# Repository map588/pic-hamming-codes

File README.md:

# PIC Parity Bit Error Detection Game

A PIC16F818 microcontroller-based educational game that teaches error detection using Hamming code parity bits through an interactive LED matrix display.

## Project Overview

This project implements a 4x4 LED grid game where players must identify and correct single-bit errors in transmitted data using parity bits. The system displays random data with intentional errors, and players use buttons to select and correct the flipped bit. 

I was inspired to make the project by [this excellant video](https://youtu.be/wTJI_WuZSwE?si=To3kZnW4QarjRsSB) by 3Blue1Brown on youtube.  Its really good, you should go watch it, its way better than my boring assembly code. 

### Key Features
- 4x4 LED matrix displaying random data patterns
- 4 parity bit indicators showing error detection codes
- Interactive button controls for bit selection and confirmation
- Visual feedback for correct/incorrect solutions
- Random number generation for varied gameplay

## Game Mechanics

1. **Display**: A 4x4 grid shows random on/off LEDs representing transmitted data
2. **Parity Bits**: 4 LEDs indicate parity for different bit groupings:
   - Bit 0: Columns 1 and 3 parity
   - Bit 1: Columns 2 and 4 parity  
   - Bit 2: Rows 1 and 3 parity
   - Bit 3: Rows 2 and 4 parity
3. **Objective**: Identify which bit in the 4x4 grid has been flipped
4. **Controls**:
   - Selection button: Cycle through grid positions (current selection blinks)
   - Confirm button: Lock in selection and check answer
   - Reset button: Generate new puzzle

### Feedback System
- **Correct Answer**: Diagonal checkmark animation on grid, all parity bits flash
- **Wrong Answer**: X pattern on grid, parity bits alternate

## Hardware

### Components
- **Microcontroller**: PIC16F818
- **Display**: 4x4 LED matrix + 4 parity indicator LEDs
- **Input**: 3 push buttons (select, confirm, reset)
- **Power**: Standard 5V supply

### Circuit Design
- Custom PCB design created in KiCad
- Surface-mount components for compact design
- ICSP programming header for development

*Custom PCB layout showing component placement and routing*

*Circuit schematic with PIC16F818 microcontroller and LED matrix*

*Final assembled PCB showing the completed hardware*

## Software

### Architecture
- **Language**: PIC Assembly (MPASM)
- **Random Number Generator**: X-ABC algorithm implementation
- **Interrupt Handling**: Button debouncing and timing
- **Display Control**: LED matrix multiplexing
- **Game Logic**: Hamming code parity calculation and verification

### Key Technical Challenges

#### Interrupt-Driven Display Multiplexing
The most complex aspect was implementing precise timer interrupt handling for LED matrix control:

- **8-bit Timer Interrupt**: With only an 8-bit timer, careful cycle counting was required to utilize the interrupt effectively 
- **Manual Context Switching**: PIC16F818 has no automatic stack - all register preservation (W, STATUS, FSR) must be handled manually in the ISR
- **Dual Display Timing**: The interrupt cycles through two 4x4 display boards, using an 8-pin indexing system
- **Memory Architecture**: 4 bytes per board (8 total), with MSB controlling row transistors and 4 LSBs selecting column LEDs
- **Persistence of Vision**: Timer frequency tuned so LEDs appear continuously lit despite sequential scanning
- **Input Responsiveness**: ISR timing balanced to maintain button polling responsiveness - if interrupts run too long, user input is missed

This required hours of timing analysis and empirical tuning to achieve both visual persistence and real-time user interaction.

#### Bit-by-Bit Board Traversal Edge Cases
The scan_routine implements a complex state machine for traversing the 4x4 board one bit at a time, with several critical edge cases:

- **Bit Position Tracking**: BITCOUNTER (0-3) tracks position within each row, while BITCHECK holds the actual bit mask being shifted left via `rlf` to traverse columns
- **Row Boundary Detection**: When BITCOUNTER reaches 4 (checked via `btfsc BITCOUNTER,2`), the end_row routine handles:
  - XORing the last bit of the current row
  - Incrementing FSR to move to the next row
  - Resetting BITCOUNTER to 0 and BITCHECK to 0x18 for the next row
- **Special First Bit Handling**: When BITCOUNTER is 0 (start of row), a different literal is XORed with the COPY board due to the boundary with the column bits 
- **ROWCHECK Wraparound**: ROWCHECK tracks the current row (0x24-0x27 for BOARDCPY), with bit 3 tested to detect when all 4 rows are complete, triggering a reset to the first row
- **Debounce Timing**: Each button press includes a delay (0xC0) to prevent multiple triggers from a single press while maintaining responsiveness

This state machine allows users to select any single bit in the 4x4 grid despite having only one selection button, by cycling through all 16 positions sequentially.

#### Automatic Board Swapping via Timer Interrupt
The system implements an elegant visual effect where two boards (BOARDPTR and BOARDCPY) are "automagically" swapped at human-visible intervals:

- **Timer-Driven Display**: TMR0 overflow triggers the interrupt service routine, which calls `display_both`
- **Asymmetric Display Timing**: 
  - BOARDPTR displays for 16 iterations (4 LEDs × 4 rows × 255 delay cycles)
  - BOARDCPY displays for 64 iterations (4× longer) to emphasize the modified state
  - This creates a visual "blink" effect where changes are clearly visible
- **Memory Layout**: Two consecutive 4-byte blocks in RAM:
  - BOARDPTR (0x20-0x23): Original puzzle state
  - BOARDCPY (0x24-0x27): User-modified state with bit flips
- **Multiplexed Column Driving**: PORTB drives transistor bases with patterns 0x08, 0x04, 0x02, 0x01 to enable each column sequentially
- **Human Persistence of Vision**: Cycling through all positions (faster than ~30Hz) makes both boards appear simultaneously lit with the modified bits appearing to blink

## Project Structure

```
├── hardware/
│   ├── pcb/              # KiCad PCB files
│   ├── schematics/       # Schematic designs
│   ├── gerbers/          # Manufacturing files
│   └── libraries/        # Custom component libraries
├── software/
│   ├── src/              # PIC assembly source code
├── docs/
│   ├── images/           # Project photos and screenshots
│   ├── datasheets/       # Component specifications
│   └── Final_Project_Idea.txt  # Original project concept
└── manufacturing/        # Production files
```

## License

This project is open source and available for educational use. The random number generator algorithm is freely available but not suitable for cryptographic applications.

---

*Developed as a final project demonstrating embedded systems design, PCB layout, and error detection algorithms.*

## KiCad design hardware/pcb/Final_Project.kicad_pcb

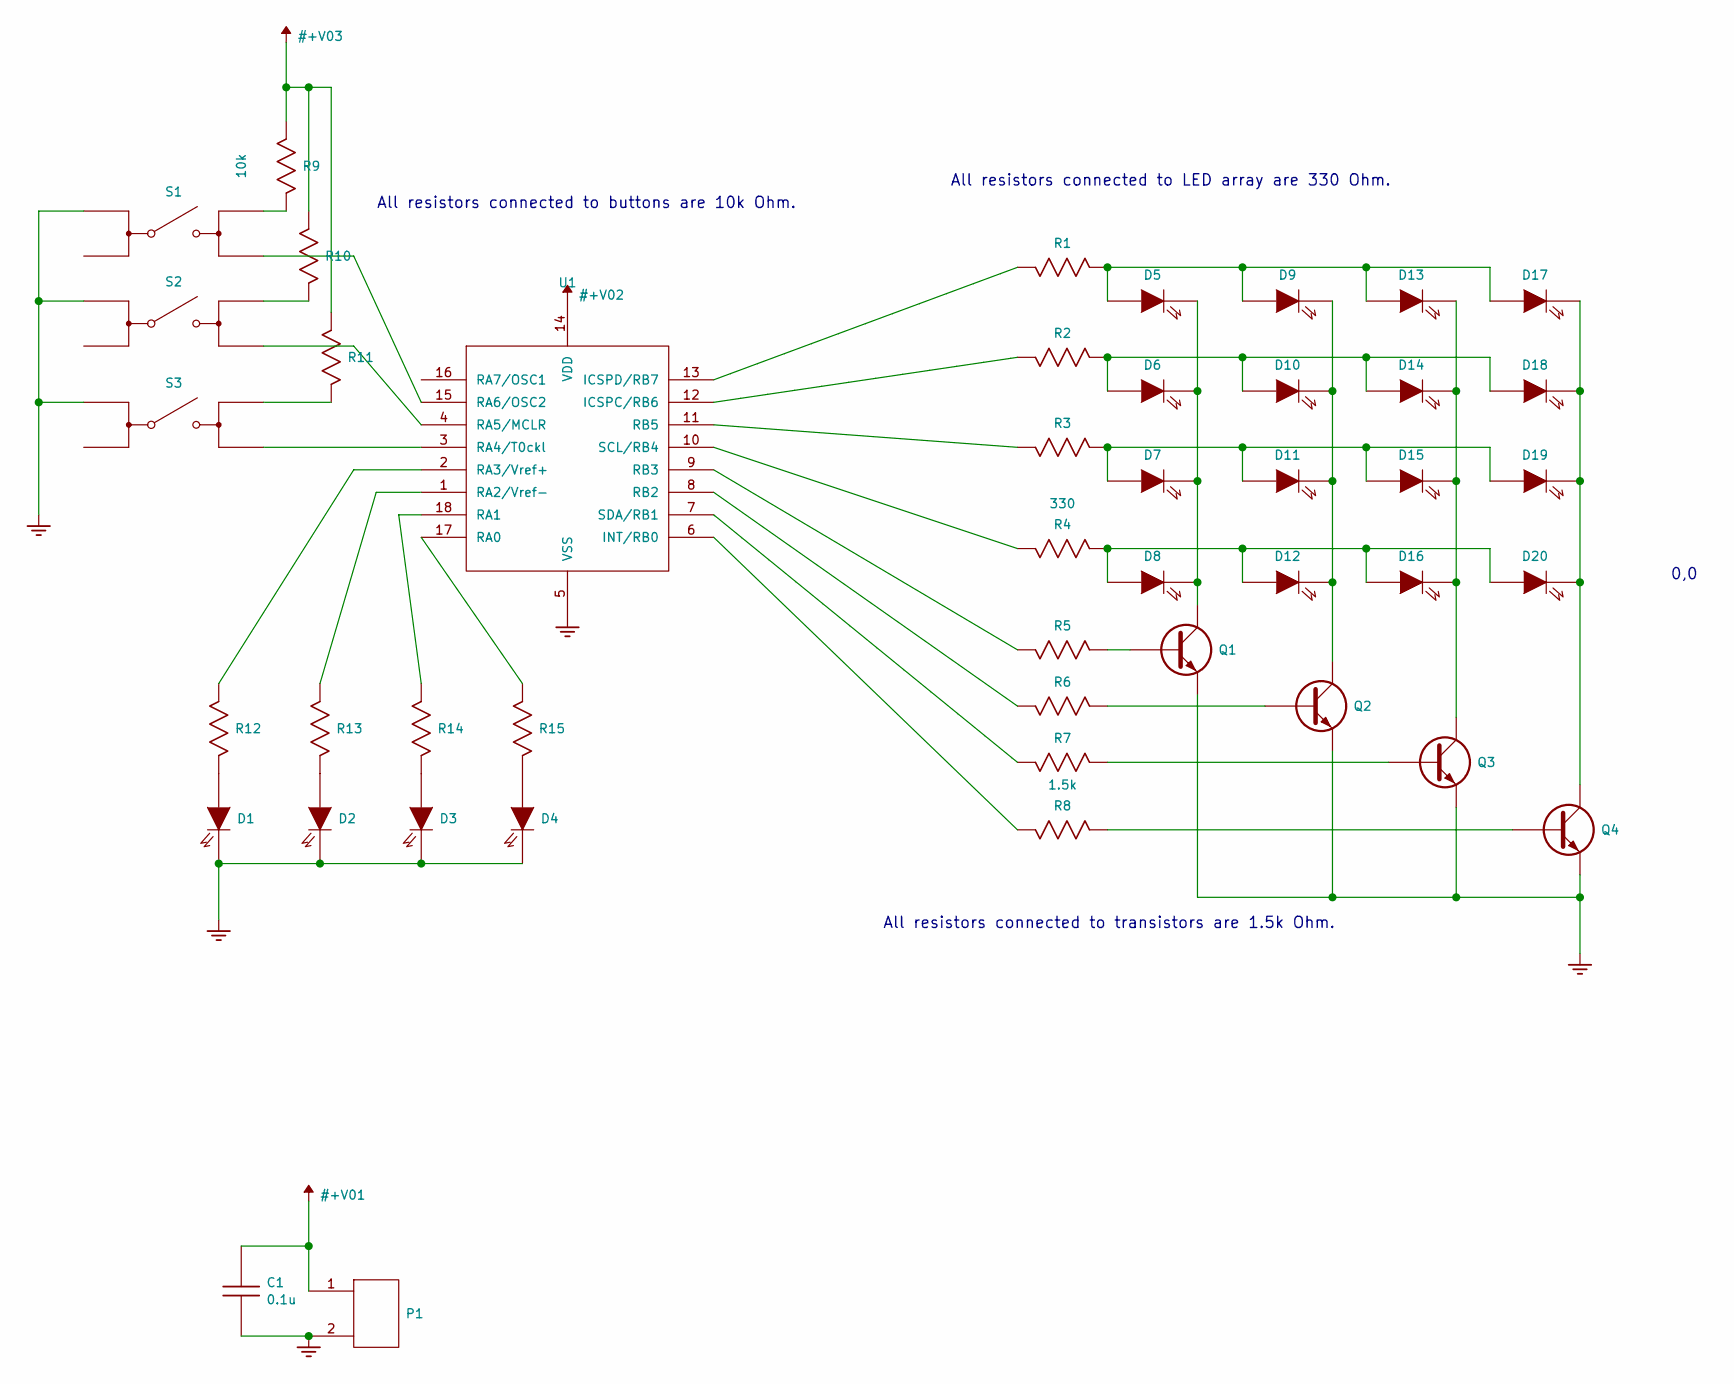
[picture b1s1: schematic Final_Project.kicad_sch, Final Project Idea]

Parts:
C1: 0.1u; SM1206
D1, D2, D3, D4, D5, D6, D7, D8, D9, D10, D11, D12, D13, D14, D15, D16, D17, D18, D19, D20: SVC_LED; SM1206-D_LED
P1: SVC_CONN_2PIN; 2-PIN-Power
Q1, Q2, Q3, Q4: SVC_Q_MMBT3904L; SOT23
R1, R2, R3, R4, R12, R13, R14, R15: 330; SM1206-R_C
R5, R6, R7, R8: 1.5k; SM1206-R_C
R9, R10, R11: 10k; SM1206-R_C
S1, S2, S3: SVC_BUTTON_SWITCH; BUTTON-SWITCH-SPST
U1: SVC_PIC16F818-18PDIP; SM_DIP18-300

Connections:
+V: C1.1, P1.1, R9.1, R10.1, R11.1, U1.14 (VDD)
GND: C1.2, D1.2 (K), D2.2 (K), D3.2 (K), D4.2 (K), P1.2 (PM), Q1.2 (E), Q2.2 (E), Q3.2 (E), Q4.2 (E), S1.3, S2.3, S3.3, U1.5 (VSS)
unnamed: D1.1 (A), R12.2
unnamed: D2.1 (A), R13.2
unnamed: D3.1 (A), R14.2
unnamed: D4.1 (A), R15.2
unnamed: D5.2 (K), D6.2 (K), D7.2 (K), D8.2 (K), Q1.3 (C)
unnamed: D6.1 (A), D10.1 (A), D14.1 (A), D18.1 (A), R2.1
unnamed: D9.2 (K), D10.2 (K), D11.2 (K), D12.2 (K), Q2.3 (C)
unnamed: D7.1 (A), D11.1 (A), D15.1 (A), D19.1 (A), R3.1
unnamed: D8.1 (A), D12.1 (A), D16.1 (A), D20.1 (A), R4.1
unnamed: D5.1 (A), D9.1 (A), D13.1 (A), D17.1 (A), R1.1
unnamed: D13.2 (K), D14.2 (K), D15.2 (K), D16.2 (K), Q3.3 (C)
unnamed: D17.2 (K), D18.2 (K), D19.2 (K), D20.2 (K), Q4.3 (C)
unnamed: Q1.1 (B), R5.1
unnamed: Q2.1 (B), R6.1
unnamed: Q3.1 (B), R7.1
unnamed: Q4.1 (B), R8.1
unnamed: R1.2, U1.13 (ICSPD/RB7)
unnamed: R2.2, U1.12 (ICSPC/RB6)
unnamed: R3.2, U1.11 (RB5)
unnamed: R4.2, U1.10 (SCL/RB4)
unnamed: R5.2, U1.9 (RB3)
unnamed: R6.2, U1.8 (RB2)
unnamed: R7.2, U1.7 (SDA/RB1)
unnamed: R8.2, U1.6 (INT/RB0)
unnamed: R9.2, S1.1
unnamed: R10.2, S2.1
unnamed: R11.2, S3.1
unnamed: R12.1, U1.2 (RA3/Vref+)
unnamed: R13.1, U1.1 (RA2/Vref-)
unnamed: R14.1, U1.18 (RA1)
unnamed: R15.1, U1.17 (RA0)
unnamed: S1.2, U1.15 (RA6/OSC2)
unnamed: S2.2, U1.4 (RA5/MCLR)
unnamed: S3.2, U1.3 (RA4/T0ckl)

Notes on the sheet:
All resistors connected to buttons are 10k Ohm.
All resistors connected to transistors are 1.5k Ohm.
All resistors connected to LED array are 330 Ohm.
0,0

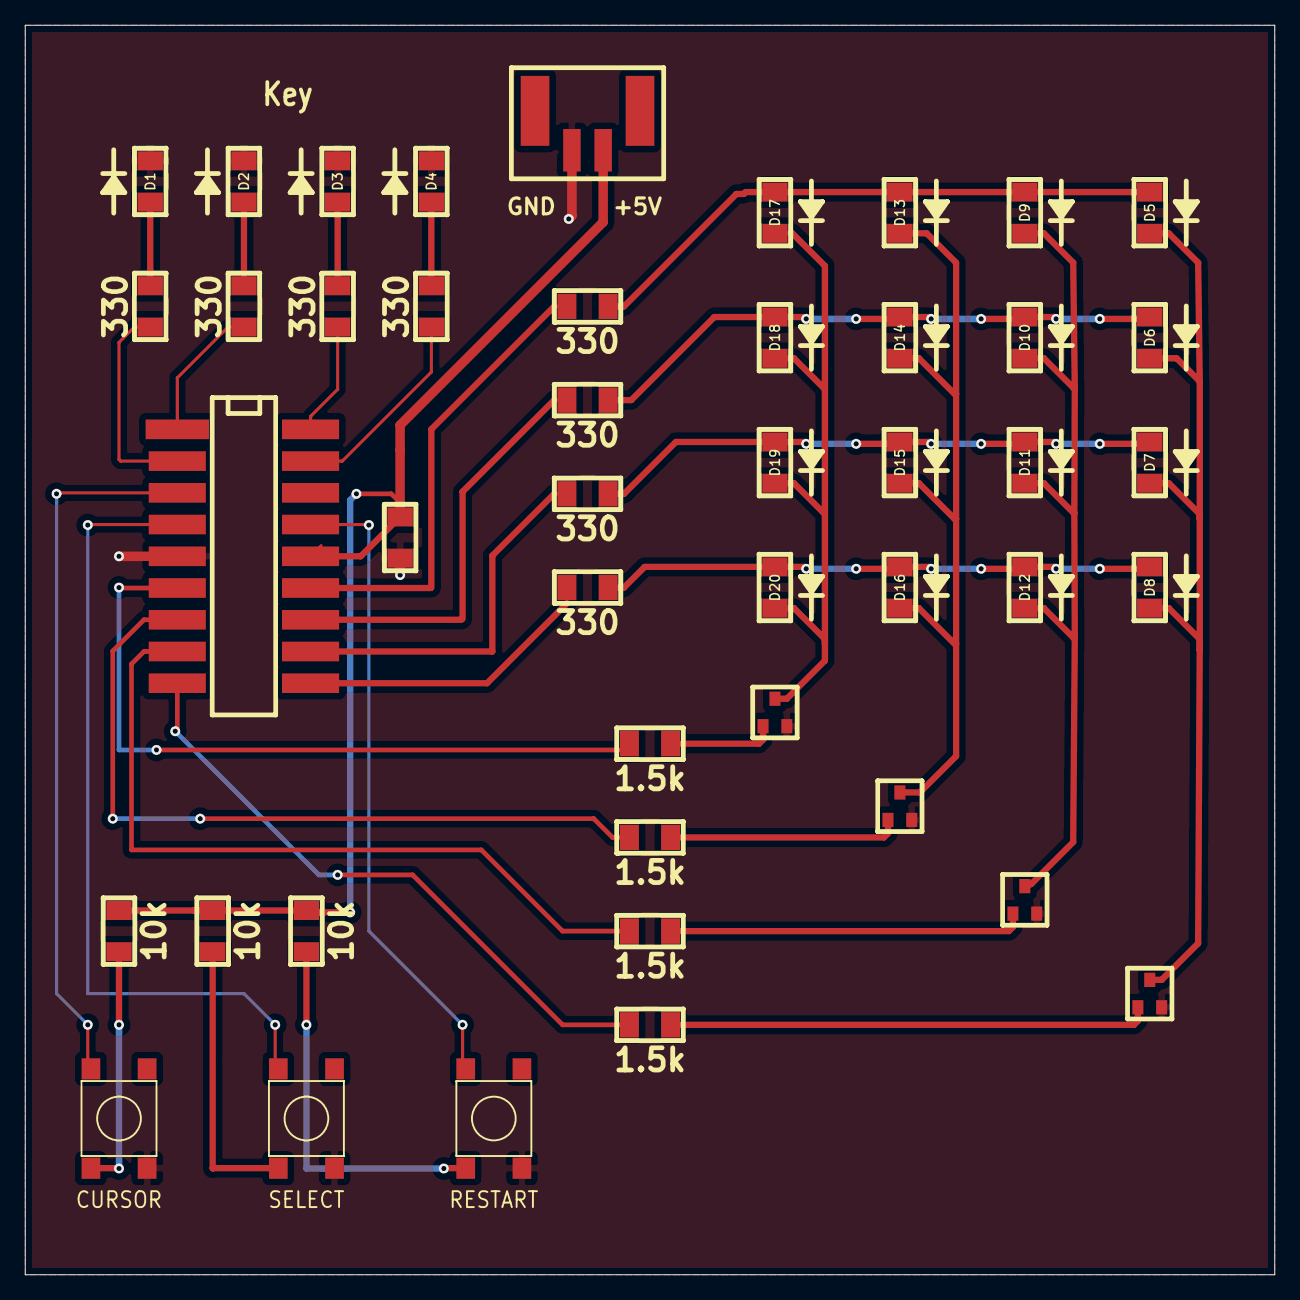
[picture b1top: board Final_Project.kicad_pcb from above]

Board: 2 copper layers, 100.0 x 100.0 mm, 45 parts (0 on the bottom side), 36 nets.

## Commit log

2025-08-21 Uploading files
2025-08-21 fixup! Merge branch 'master'
2025-08-21 Added 3Blue1Brown video to README.
2025-09-08 Fix typo in README
